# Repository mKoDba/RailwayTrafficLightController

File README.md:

# Railway Traffic Light Controller
Railway Traffic Light Controller Project

This is a faculty project for the fall semester of year 2018/2019 done at FEUP (Faculdade de Engenharia da Universidade do Porto) as part of the course Eletronic Systems/Sistemas Electrónicos (SELE).

Authors are Joel Vaz and Mario Kodba.

Goals of the project are:

- design a robust railway traffic light control system, which controls one green and one red light, based on a microcontroller ATMEGA328p

- use two types of communication protocols (synchronous and asynchronous)

- use memory testing algorithms

- follow and stick to particular coding guideline (for example MISRA C)

- use professional development methodology: project management, proper debugging techniques, use of version control

- design and implement the laboratorial prototype using LEDS, sensors and microcontroller

- design electrical scheme and PCB industrial prototype using EAGLE CAD

TODO:
* finish memory testing
* add i2c timeout if not detected
* add watchdog

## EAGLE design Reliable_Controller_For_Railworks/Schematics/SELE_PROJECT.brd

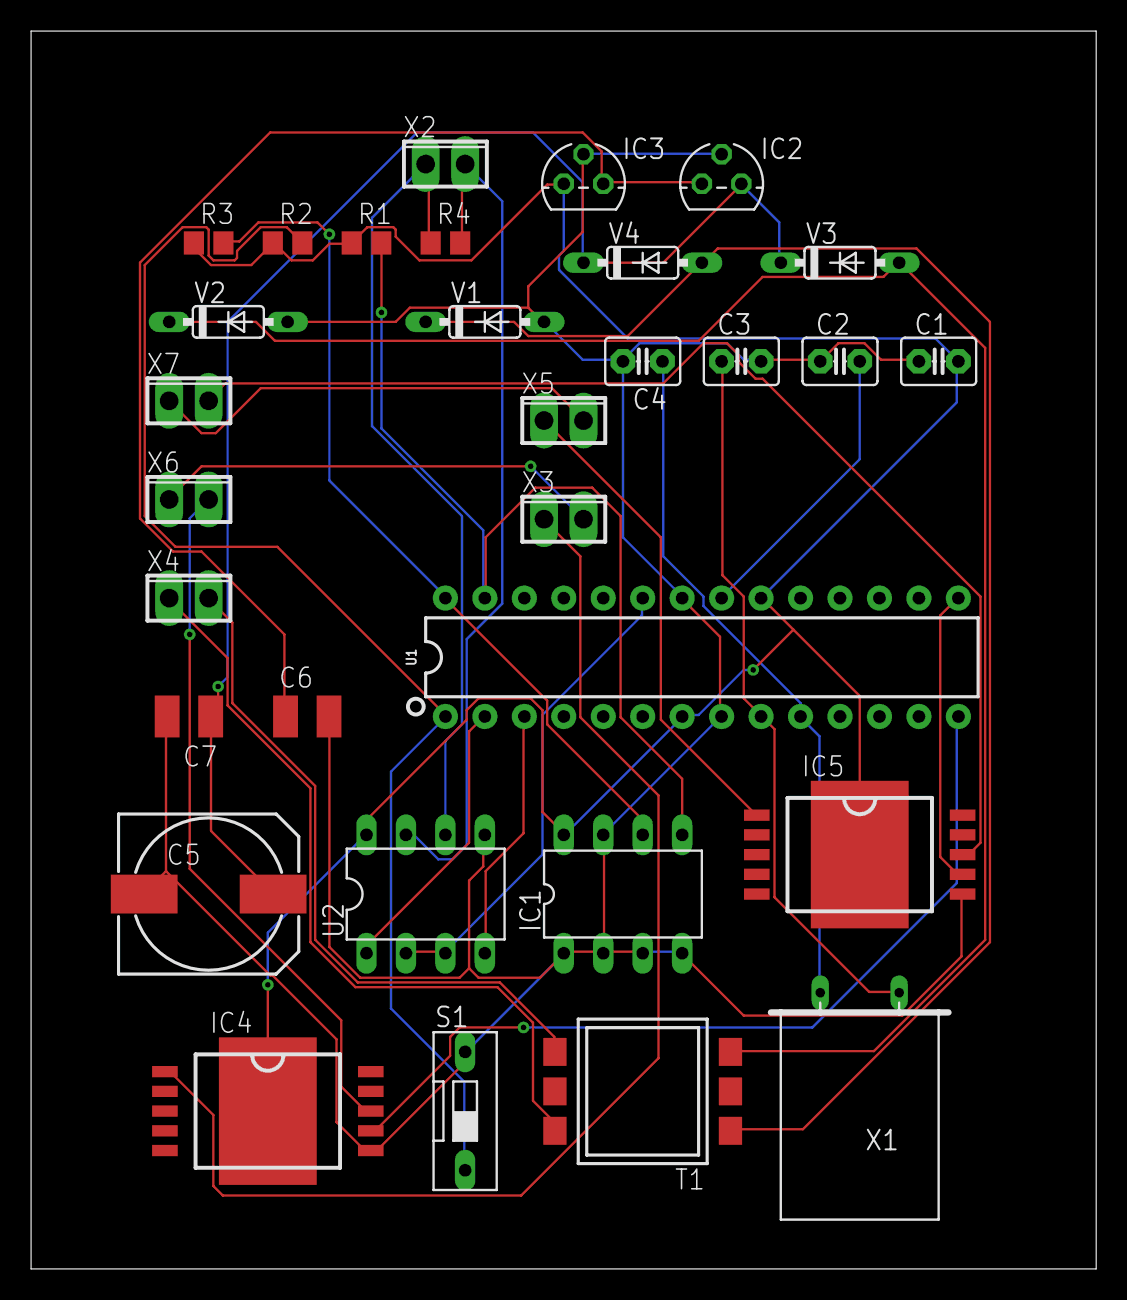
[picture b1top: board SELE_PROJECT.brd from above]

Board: 2 copper layers, 68.6 x 79.7 mm, 31 parts (0 on the bottom side), 27 nets.

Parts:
C1, C2: 100n; C2.5-3
C3, C4: 22p; C2.5-3
C5: 1500u/35V; 150CLZ-1010
C6, C7: 0.1u; C1210
IC1: D1 (24LC1025); DIL08
IC2: D2 (7812L); TO92
IC3: D3 (7805L); TO92
IC4, IC5: VN460SP; POWER-SO10
R1, R3: 10k; R0805
R2: 47k; R0805
R4: 120; R0805
S1: DS-01
T1: 230V to 12V AC; SM-EP7
U1: 328P; MICROCONTROLLER_DIP28
U2: LTC485N; DIL08
V1, V2, V3, V4: 1N4148DO35-7; DO35-7
X1: 16MHz; Q
X2: 2POL254
X3, X5: LAMP CONNECTOR; 2POL254
X4, X6, X7: 230V AC CONNECTOR; 2POL254

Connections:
GND: C1.1, C2.1, C3.2, C4.2, C5.-, C6.2, C7.2, IC1.1, IC1.2, IC1.3, IC1.4, IC1.7, IC2.2, IC3.2, IC4.6, IC5.6, S1.2, U1.8, U1.22, U2.5, V1.A, V2.A
unnamed: C4.1, U1.10, X1.2
unnamed: U1.2, U2.1
unnamed: IC1.5, R1.2, U1.27
unnamed: U1.3, U2.4
unnamed: IC1.6, R3.2, U1.28
unnamed: R4.1, U2.6, X2.1
unnamed: U1.23, U2.2, U2.3
unnamed: R2.2, S1.1, U1.1
unnamed: R4.2, U2.7, X2.2
unnamed: C2.2, U1.21
unnamed: T1.6, V1.C, V4.A
unnamed: T1.4, V2.C, V3.A
unnamed: T1.1, X4.1
unnamed: T1.2, T1.3, X4.2
unnamed: IC4.7, U1.14
unnamed: C5.+, C7.1, IC2.3, V3.C, V4.C
unnamed: C6.1, IC2.1, IC3.3
unnamed: IC5.7, U1.15
unnamed: IC4.1, X3.1
unnamed: IC5.1, X5.1
unnamed: IC4.8, X6.2
unnamed: X3.2, X6.1
unnamed: IC5.8, X7.2
unnamed: X5.2, X7.1
VCC: C1.2, IC1.8, IC3.1, IC4.P, IC5.P, R1.1, R2.1, R3.1, U1.7, U1.20, U2.8
X1: C3.1, U1.9, X1.1

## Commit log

2018-11-21 Added the main structural project files
    A simple Main.c that uses the ATMEGA328p internal clock and turns on a LED
    EEPROM simple memory pattern test, reads and writes into the EEPROM
    Configuration file for the project
2018-11-21 C style coding guideline
    Important to read and respect during the elaboration of the project
    This will be our primary coding guideline based on NASA system software
2018-11-21 Set theme jekyll-theme-minimal
2018-11-22 This is an Hello World test commit
    Version 0
    TODO Everything about the project
2018-11-22 Commit test number 2
    Hello World
    TODO ignore this commit
    Everything about project
2018-11-22 This is commit number 3
    Hello World
2018-11-22 Commit number 4
    Hello World
    #ignore this commit
2018-11-26 Added Comments
    Updated the comment section of code using the NASA C style code
    guidelines.
2018-11-29 Added new source files to the project
    TODO - Create the specific functions
    Create the EagleCAD design
    Test the code
2018-12-04 Added new config file for interface with Visual studio code
2018-12-04 Configuring VScode
2018-12-04 VSCODE TEST
2018-12-05 VS Code test commit
2018-12-05 This commit adds a new schedule planning tasks for the next two weeks
2018-12-05 Updated Code with serial communication functions implemented
2018-12-05 added i2c communication protocol
2018-12-05 added header files for i2c
2018-12-05 added i2c testing, pointer to input string
2018-12-05 Fixed some bugs on i2c. Noticed that VS code is set up for ATMEGA328pb need to change
2018-12-05 Added headers to the inc folder. Organization only commit
2018-12-07 Git commit with updated library paths for VS Code
2018-12-07 Serial Communication is able to receive strings. Controller checks for id in message.
2018-12-07 Added comments to code.
2018-12-10 Add files via upload
    Schematic drawing with uC, EEPROM and PC serial communication
    -missing lamp interface
2018-12-10 Updated file folders
2018-12-10 Added new include file and new source file for light controller logic.
2018-12-10 Fixed a small bug
2018-12-11 Updated controller.c code and fixed bug in main.c
2018-12-12 # WARNING: head commit changed in the meantime
    Merge branch 'master' of
    https://github.com/sobakaAxolotl/RailworkController
    Conflicts:
    Reliable_Controller_For_Railworks/inc/serial_comms.h
    Reliable_Controller_For_Railworks/src/main.c
    Reliable_Controller_For_Railworks/src/serial_comms.c
2018-12-12 added functions
2018-12-12 added header functions
2018-12-12 .project change??
2018-12-12 everything
2018-12-12 Added i2c enable signal
2018-12-12 Added miniterm py for serial port monitoring
2018-12-12 Controller Logic implemented. Updated TODO file. Fixed bug in Serial communication.
2018-12-12 Added defines to config.h file in order to clean main.c
2018-12-12 added i2c_init to main.c
2018-12-13 Added new documment with ATmega328p pins I/O scheme
2018-12-16 Debug mode for java serial reader enabled
2018-12-17 added writing/reading to/from eeprom memory
2018-12-17 added functions and headers for reading/writing eeprom memory
2018-12-17 Added debug mode for serial communication java program.
2018-12-17 Improved debug mode
    Improved debug mode
2018-12-17 Fixed Led on&off function bug. TO FIX - > I2C blocks the main cycle.
2018-12-17 minor fix for printing
2018-12-17 minor printing fixes
2018-12-17 added cmdServer cleaning values as it wasn't receiving correct values when
2018-12-18 added saving address on power off + debug changes
2018-12-18 changed eeprom mem test to ram test + other
2018-12-18 minor change to ram_test.c
2018-12-18 added flash mem test, needs testing and checking
2018-12-18 updated electrical schematic
2018-12-18 schematic update
2018-12-18 updated schematic
2018-12-18 Implemented watch dog timer.
2018-12-18 EEPROM problem detected
    EEPROM read is not working correctly :(
2018-12-20 Includes in right folder for organization. TODO updated!
2018-12-25 Added Comments to code
2018-12-27 Minor bug fix and implementation of log printing in a server command
2019-01-03 Finish
    Finish Project
2019-02-17 rename
2019-02-17 added comments
2019-02-18 added project gantogram
